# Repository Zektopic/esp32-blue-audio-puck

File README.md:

# BlueAudio Puck

**Turn wired headphones wireless.** A pocket-sized Bluetooth audio receiver: it
pairs with a phone or computer as an A2DP sink, decodes the stream on an ESP32,
runs it through a parametric equaliser, and pushes PCM out over I²S to an
external DAC and headphone amplifier feeding a 3.5 mm jack.

-informational)

> [!IMPORTANT]
> **Original ESP32 only.** A2DP rides on Bluetooth Classic (BR/EDR), which
> Espressif removed from the ESP32-S3 and ESP32-C3. Those parts are BLE-only and
> cannot run this firmware — and they cannot fall back to LE Audio either, since
> that needs BLE 5.2 isochronous channels and they are 5.0.

---

## What it does

| | |
| --- | --- |
| **A2DP sink** | Pairs as a headphone. SBC decode, 16/32/44.1/48 kHz, mono or stereo. |
| **I²S output** | 16-bit PCM to an external DAC. APLL-clocked for accurate 44.1 kHz. |
| **AVRCP, both roles** | Phone's volume slider works; track metadata comes back; buttons drive transport. |
| **Parametric EQ** | Five biquad bands per channel, sample-rate aware, ~16% of one core when fully active. |
| **OLED status screen** | 128x64 SSD1306 over I2C: signal, track, artist, transport, volume, battery. |
| **Battery gauge** | ADC on a divider, Li-po curve, low and critical warnings. |
| **Physical UI** | One multi-function button, optional volume keys, optional PWM status LED. |
| **Power policy** | Capped TX power, 80–160 MHz frequency scaling, deep sleep on idle. |
| **Bounded pairing** | Discoverable only when you ask for it, not permanently. |

## Signal chain

```mermaid
flowchart LR
    SRC["Phone / PC<br/><i>A2DP source</i>"]
    subgraph PUCK["BlueAudio Puck"]
        direction LR
        BT["ESP32<br/>Bluedroid A2DP sink<br/>SBC decode"]
        DSP["Ring buffer<br/>+ EQ + volume"]
        DAC["PCM5102A<br/>I²S DAC"]
        AMP["Headphone amp"]
        OLED["SSD1306 OLED<br/><i>I²C</i>"]
        BATT["Li-po + divider<br/><i>ADC</i>"]
    end
    JACK["3.5 mm<br/>headphones"]

    SRC -- "Bluetooth Classic" --> BT
    BT -- "PCM frames" --> DSP
    DSP -- "I²S" --> DAC
    DAC -- "line level" --> AMP
    AMP --> JACK
    BT -. "track, volume" .-> OLED
    BATT -. "percent" .-> OLED
```

## Firmware architecture

The single rule everything else follows: **Bluedroid callbacks only enqueue.**
Anything slow in stack context stalls the radio and comes out as dropouts.

```mermaid
flowchart TD
    subgraph BTCTX["Bluetooth stack context — never blocks"]
        A2DP["A2DP data callback"]
        EVT["GAP / A2DP / AVRCP<br/>event callbacks"]
    end
    subgraph APPCTX["Application task — core 0"]
        WORK["work dispatcher<br/><i>bt_core</i>"]
    end
    subgraph AUDCTX["Audio writer task — core 1"]
        RB[("ring buffer<br/>32 kB")]
        EQ["biquad cascade<br/><i>audio_dsp</i>"]
        VOL["volume gain"]
        I2S["i2s_channel_write"]
    end

    A2DP -- "non-blocking send" --> RB
    EVT -- "dispatch" --> WORK
    WORK -- "start / stop / format" --> RB
    RB --> EQ --> VOL --> I2S

    classDef ctx fill:none,stroke-dasharray:4 3
    class BTCTX,APPCTX,AUDCTX ctx
```

Every cost — the blocking I²S write, the EQ, the gain — lives on the writer
task, pinned to the core the radio is not using.

### Components

| Component | Responsibility |
| --- | --- |
| [`bt_core`](components/bt_core/) | Stack bring-up, work queue between Bluedroid and the app task, bond management |
| [`audio_sink`](components/audio_sink/) | I²S channel, ring buffer, writer task, volume gain |
| [`audio_dsp`](components/audio_dsp/) | Parametric biquad equaliser and its benchmark |
| [`puck_avrcp`](components/puck_avrcp/) | AVRCP controller and target: volume, metadata, transport keys |
| [`puck_ui`](components/puck_ui/) | Button gestures and PWM status LED |
| [`puck_display`](components/puck_display/) | SSD1306 panel driver, framebuffer, screens |
| [`puck_battery`](components/puck_battery/) | ADC sensing and the Li-po discharge curve |
| [`puck_power`](components/puck_power/) | TX power, frequency scaling, idle deep sleep |

These are written from scratch against the IDF v5.5 API rather than reusing the
ESP-IDF example's shared components, which are pulled in by `${IDF_PATH}` path
and would make the repository unbuildable anywhere else. See
[docs/design-notes.md](docs/design-notes.md) for what that surfaced.

## Hardware

The pin map follows the layout that lets a PCM5102A board sit **directly under**
an ESP32 devkit on short solder bridges, rather than the pins that happen to be
convenient on a breadboard.

| ESP32 | Signal | Goes to |
| --- | --- | --- |
| GPIO 4 | I²S BCK | PCM5102A `BCK` |
| GPIO 15 | I²S LRCK | PCM5102A `LRCK` |
| GPIO 2 | I²S DATA | PCM5102A `DIN` |
| GPIO 21 | I²C SDA | SSD1306 `SDA` |
| GPIO 22 | I²C SCL | SSD1306 `SCL` |
| GPIO 32 | BT1 | to GND — next track / volume up |
| GPIO 33 | BT2 | to GND — play/pause / pairing (RTC pin, wakes from deep sleep) |
| GPIO 27 | BT3 | to GND — previous track / volume down |
| GPIO 35 | Battery sense | divider midpoint (optional, unfitted by default) |
| 3V3, GND | Power | both boards |

> [!NOTE]
> **No MCLK/SCK wire to the DAC.** Solder the `SCK` bridge on the front of the
> PCM5102A instead and it derives its own clock from BCK. Leave the ESP32 pin
> beneath it unconnected — a strip of tape stops it shorting to anything.

> [!IMPORTANT]
> **GPIO 2 is the devkit's on-board LED pin and a strapping pin.** It now
> carries I²S data, so the on-board LED flickers with audio — harmless, and the
> reason `PUCK_LED_GPIO` defaults to *not fitted*. It also means the board may
> refuse to enter download mode if the DAC holds that line high during reset;
> holding **BOOT** while flashing works around it.

PCM5102A jumpers — these cause most "no sound" reports:

| Pin | Set to | Why |
| --- | --- | --- |
| SCK bridge | **soldered** | Runs the internal PLL, so no MCLK wire is needed |
| XSMT | 3V3 | Release soft-mute. Low means muted. |
| FMT | GND | I²S (Philips) frame format, which is the firmware default |
| FLT | GND | Normal latency filter |
| DEMP | GND | De-emphasis off |

**Battery sensing** is optional and off by default. To fit it, run a divider
from the cell to GPIO 35 — two 100 kΩ resistors give 2:1, fits the ADC range
with a full 4.2 V cell, and draws about 21 µA — then set
`PUCK_BATTERY_ADC_GPIO=35` and the ratio to match your resistors.

Full parts discussion, power budget and the roadmap to a custom board:
[docs/hardware.md](docs/hardware.md).

## Building

Requires **ESP-IDF v5.5.4**.

```powershell
& 'C:\Espressif\tools\Microsoft.v5.5.4.PowerShell_profile.ps1'
idf.py set-target esp32
idf.py build
idf.py -p COM10 flash monitor
```

`sdkconfig` is generated and gitignored; `sdkconfig.defaults` is the source of
truth. Project settings live under **BlueAudio Puck** in `idf.py menuconfig`.

Expected first output:

```
I (593) puck: BlueAudio Puck booting (IDF v5.5.4)
I (603) audio_sink: ready: bck=4 ws=15 dout=2, 32 kB buffer, prefetch 25%
I (603) audio_dsp: 5-band equaliser ready at 44100 Hz (off, 0 active)
I (613) ssd1306: 128x64 panel at 0x3c on SDA=21 SCL=22
I (1313) bt_core: controller up, address ...
I (1373) puck: no bonded sources; discoverable as "BlueAudio Puck"
```

> [!TIP]
> If flashing fails with `Wrong boot mode detected (0x13)`, hold the **BOOT**
> button as the flash starts. Some devkits — and any board where GPIO 2 is
> loaded by the DAC — will not auto-reset into download mode.

## Using it

| Button | Tap | Hold |
| --- | --- | --- |
| **BT1** | Next track | Volume up — repeats while held |
| **BT2** | Play / pause | Pairing window (1.5 s) · forget all bonds (5 s) |
| **BT3** | Previous track | Volume down — repeats while held |

One action per press, no multi-tap timing to get right. Holding a volume button
sweeps rather than nudging once, at roughly four seconds end to end.

### The screen

| Screen | When |
| --- | --- |
| Splash | While the stack comes up |
| `PAIRING` | Discoverable, waiting for a source |
| `IDLE` | Connectable, nothing connected |
| Now playing | Signal, track and artist, transport state, volume bar, battery |

The top-left **signal meter** shows link quality while a source is connected.
It is hidden when nothing is connected, because bars against no link would be
meaningless. Note what Bluetooth Classic actually reports — see below.

The track title scrolls when it is too long, pausing at each end — continuous
sliding is much harder to read. Volume changes raise a brief toast over the
bottom of the screen. Battery shows as a percentage and an icon, or `USB` when
no sense divider is fitted.

> [!NOTE]
> **The signal meter will usually read full, and that is correct.** Bluetooth
> Classic does not report absolute signal strength. It reports a delta from the
> *Golden Receive Power Range* — the window the controller works to keep the
> link inside — so **zero means healthy**, not "no signal". The value only goes
> negative once the link is genuinely struggling. Read the bars as *fine /
> getting worse / about to drop out*, not as dBm.

At start-up the panel runs a **self test** — solid fill, checkerboard, then a
border — before any text is drawn. None of it uses the font, which is the
point: it separates a bus or panel fault from a text-rendering fault.

### The optional LED

| LED | Meaning |
| --- | --- |
| Fast blink | Discoverable, waiting for a source |
| Slow breathe | Connected, not streaming |
| Steady dim | Audio playing |
| Triple flash | Something failed to start |

Unfitted by default, because GPIO 2 now carries I²S data and the screen shows
the same states in words.

Volume normally comes from the phone over AVRCP absolute volume. Dedicated
volume buttons are optional and unfitted by default.

## Configuration

All under `idf.py menuconfig` → **BlueAudio Puck**. Every GPIO accepts `-1` for
"not fitted".

| Option | Default | Notes |
| --- | --- | --- |
| `PUCK_BT_DEVICE_NAME` | `BlueAudio Puck` | Shown in the pairing list |
| `PUCK_I2S_BCK/LRCK/DOUT_GPIO` | 4 / 15 / 2 | Direct-solder layout |
| `PUCK_I2C_SDA/SCL_GPIO` | 21 / 22 | `-1` disables the display |
| `PUCK_DISPLAY_I2C_ADDRESS` | 0x3C | Some modules strap to 0x3D |
| `PUCK_DISPLAY_CONTRAST` | 127 | |
| `PUCK_DISPLAY_SELF_TEST` | on | ~1.4 s of boot time |
| `PUCK_RSSI_POLL_SECONDS` | 3 | How often the signal meter updates |
| `PUCK_BATTERY_ADC_GPIO` | 35 | ADC1 pins only (32–39); `-1` if no divider |
| `PUCK_BATTERY_DIVIDER_RATIO_X100` | 200 | 2:1; must match your resistors |
| `PUCK_BT1/BT2/BT3_GPIO` | 32 / 33 / 27 | Active low, internal pull-up |
| `PUCK_VOLUME_STEP` | 6 | Per repeat, of 127 |
| `PUCK_LED_GPIO` | -1 | GPIO 2 is now I²S data |
| `PUCK_I2S_SLOT_FORMAT` | Philips | Must match the DAC's `FMT` pin |
| `PUCK_I2S_USE_APLL` | on | Accurate 44.1 kHz, slightly more current |
| `PUCK_AUDIO_RINGBUF_KB` | 32 | Larger rides out radio retries, costs RAM and latency |
| `PUCK_AUDIO_PREFETCH_PERCENT` | 25 | ≈46 ms cushion; also what an underrun costs to rebuild |
| `PUCK_AUDIO_WRITER_CORE` | 1 | Keep off core 0, which runs the radio |
| `PUCK_EQ_BANDS` | 5 | A ceiling, not a fixed price — flat bands cost nothing |
| `PUCK_EQ_ENABLED_AT_BOOT` | off | Starts transparent |
| `PUCK_EQ_BENCHMARK_AT_BOOT` | off | Times the cascade; see below |
| `PUCK_PAIRING_WINDOW_SECONDS` | 120 | How long a long press stays discoverable |
| `PUCK_BT_TX_POWER_LEVEL` | 7 (+9 dBm) | Ceiling; lower it for runtime |
| `PUCK_BT_TX_POWER_MIN_LEVEL` | 4 (0 dBm) | Floor power control may drop to |
| `PUCK_CPU_MAX/MIN_FREQ_MHZ` | 160 / 80 | Dynamic frequency scaling |
| `PUCK_IDLE_SLEEP_MINUTES` | 15 | Counts only while disconnected; 0 disables |

## Measured

| What | Result |
| --- | --- |
| EQ cost, 5 stereo biquad sections | 1337 µs per 360-frame block = **16% of one core** at 160 MHz |
| EQ cost per band | ~3.2% of a core, so roughly 30 sections before saturating one |
| OLED bus scan | One device ACKs at **0x3C** on SDA 21 / SCL 22 |
| Full-frame OLED refresh | 1025 bytes at 400 kHz ≈ 21 ms, hence a few Hz refresh |
| Firmware image | ~1.04 MB (needs the large single-app partition; the 1 MB default does not fit) |
| Free heap after boot | ~210 kB |
| Pairing window | Closes at 120.0 s, verified on hardware |

Power draw has **not** been measured. The estimates in
[docs/hardware.md](docs/hardware.md) are datasheet-derived, and devkit
measurements would be meaningless anyway — the USB-UART bridge and the AMS1117
regulator dominate a devkit's draw whatever the firmware does.

## Documentation

- [hardware/](hardware/) — KiCad schematic and PCB for a single-board version (unrouted, unfabricated)
- [docs/hardware.md](docs/hardware.md) — parts, wiring, power budget, board roadmap
- [docs/design-notes.md](docs/design-notes.md) — why the firmware is shaped this way, and the IDF bugs it avoids
- [docs/troubleshooting.md](docs/troubleshooting.md) — no sound, no pairing, dropouts, build failures
- [SECURITY.md](SECURITY.md) — threat model, pairing decisions, accepted risks

## Status

Working: builds, boots, pairs, advertises correctly, AVRCP negotiates, power and
UI subsystems initialise. Verified on an ESP32-WROOM devkit.

**Not yet verified:** audio actually coming out, and what the OLED renders. The
I²C bus and the panel address are confirmed by a scan on real hardware, but the
glyphs and layout have not been seen. The I²S configuration, the EQ response and
the end-to-end audio path are reasoned against the ESP-IDF v5.5.4 driver
sources, not heard. Battery sensing has no cell fitted, so only its
"not fitted" path runs.

## Prior art

Written from scratch, but these informed the design and are worth reading:

- [WillyBilly06/ESP32-A2DP-SINK-WITH-CODECS-UPDATED](https://github.com/WillyBilly06/ESP32-A2DP-SINK-WITH-CODECS-UPDATED) — LDAC/aptX/AAC patched into the IDF stack, which proves the SBC ceiling is firmware and not silicon
- [YetAnotherElectronicsChannel/ESP32_4CH_DSP_BT_AMPLIFIER](https://github.com/YetAnotherElectronicsChannel/ESP32_4CH_DSP_BT_AMPLIFIER) — parametric EQ with a Wi-Fi config UI, full schematics and gerbers
- [ESP32 as BT receiver with DSP capabilities](https://hackaday.io/project/166122-esp32-as-bt-receiver-with-dsp-capabilities) — biquads in the a2dp_sink render path; left the biquad budget as an open question, which [docs/design-notes.md](docs/design-notes.md) answers
- [gangg111/ESP32-Bluetooth-Audio-Receiver](https://github.com/gangg111/ESP32-Bluetooth-Audio-Receiver) — PCM5102A plus an OLED showing track metadata
- [pschatzmann/ESP32-A2DP](https://github.com/pschatzmann/ESP32-A2DP) — the reference Arduino-side A2DP library

## Licence

MIT — see [LICENSE](LICENSE).

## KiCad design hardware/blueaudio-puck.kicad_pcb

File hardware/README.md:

# BlueAudio Puck carrier board, rev A

KiCad 10 schematic and PCB for a single-board version of the puck: ESP32-WROOM-32U,
PCM5102A DAC, Li-po charging, two separate 3V3 rails, OLED header, three user
buttons and a 3.5 mm output — 60 × 64 mm, drawn to JLCPCB's two-layer rules.

| File | What it is |
| --- | --- |
| [`blueaudio-puck.kicad_pro`](blueaudio-puck.kicad_pro) | Project — open this |
| [`blueaudio-puck.kicad_sch`](blueaudio-puck.kicad_sch) | Schematic |
| [`blueaudio-puck.kicad_pcb`](blueaudio-puck.kicad_pcb) | Board |
| [`bom.csv`](bom.csv) | Bill of materials |
| [`preview/`](preview/) | SVG renders of both |
| [`scripts/`](scripts/) | The generator — see below |

## Read this before you order anything

> [!CAUTION]
> **Not finished: eight nets still need routing by hand.**
>
> Everything the generator lays is DRC-clean — **zero clearance violations,
> zero shorts, zero hole-clearance errors** under JLCPCB's rules. But 25 of 33
> nets are routed, not 33, and the remaining eight are unconnected copper:
>
> `+3V3A` · `AUDIO_L` · `CC1` · `CC2` · `DAC_LDOO` · `DAC_VNEG` · `I2S_BCK` · `I2S_LRCK`
>
> All eight are around the two fine-pitch parts — the TSSOP-20 DAC and the
> USB-C receptacle. Open the board in Pcbnew and its interactive router will
> finish them far faster and better than the one in `scripts/`. Do not order
> anything until DRC reports zero unconnected items.

> [!WARNING]
> **Nothing here has been fabricated or tested.** It passes ERC and the DRC
> checks that apply to an unrouted board. It has never been a physical object.
> Review the schematic against the datasheets before you spend money.

## Verification

Actually run, with the output quoted rather than summarised:

```
$ kicad-cli sch erc --severity-error --severity-warning
Found 4 violations                    # all lib_symbol_mismatch, see below

$ kicad-cli pcb drc --severity-error --severity-warning
Found 25 violations
Found 22 unconnected items
```

The schematic is clean: **zero electrical errors**, no unconnected pins, no
dangling labels, no malformed outline. All four ERC warnings are
`lib_symbol_mismatch` on KiCad's *derived* symbols — the two regulators and the
two transistors. Cosmetic; see below.

The board has **no electrical errors either**. Breaking the 25 down:

| Count | Kind | Status |
| --- | --- | --- |
| 22 | `unconnected_items` | **Must fix** — the eight unrouted nets |
| 15 | `silk_over_copper` | Cosmetic; every fab ignores it |
| 10 | `silk_overlap` | Cosmetic |

No `clearance`, no `shorting_items`, no `hole_clearance`. That took three fixes
to the router's geometry, each of which had produced copper that looked right
and was not — they are written up in the file that makes them:

- **A track is not a point.** A 0.4 mm power track centred on a 0.25 mm grid
  cell spills into its neighbours; checking only the cell it steps through let
  it sit 0.15 mm from a pad. Same for vias, which are 0.6 mm across — one
  landed on top of another net's track.
- **Clearance belongs in the check, not the map.** Growing a clearance halo
  around every pad *and* checking a track's own clearance against it demanded
  the gap twice, which makes escaping a 0.65 mm pitch TSSOP impossible.
- **Holes are stricter than copper.** Copper-to-hole is 0.25 mm where
  copper-to-copper is 0.15 mm, so drilled pads are claimed slightly larger than
  their copper.

The router still gets 25 of 33 nets rather than all of them. It routes in order
and never rips up an earlier net to make room, which is the difference between
it and a real autorouter.

The two ERC warnings are `lib_symbol_mismatch` on `AP2112K-3.3` and
`LP2985-3.3`. Both are KiCad *derived* symbols (`extends`), and the generator
flattens them to embed them; the flattened copy differs cosmetically from the
library's. Connectivity and pin numbering are unaffected. Eeschema's
*Update Symbols from Library* clears it.

The silkscreen warnings are reference designators sitting over pads. Normal for
auto-placed boards, ignored by every fab, and worth tidying only once placement
is final.

## How it is generated

Both files come from **one** netlist, in [`scripts/design.py`](scripts/design.py).

That matters more than it sounds. A schematic and a PCB authored separately
disagree about connectivity, and KiCad does not tell you until someone runs ERC
and gets a wall of errors. One source, two emitters, no drift.

```
scripts/design.py         parts, nets, no-connects, board size  <- edit this
scripts/kisym.py          pulls symbols out of the KiCad libraries
scripts/check_sheet.py    catches stubs from different nets touching
scripts/gen_schematic.py  emits the .kicad_sch
scripts/gen_pcb.py        emits the .kicad_pcb (needs KiCad's python)
```

To regenerate:

```bash
cd hardware/scripts
python design.py          # netlist self-check
python check_sheet.py     # no two nets touching
python gen_schematic.py
"C:/Users/manup/AppData/Local/Programs/KiCad/10.0/bin/python.exe" gen_pcb.py
```

`gen_pcb.py` needs KiCad's bundled interpreter — `pcbnew` lives only there.

Symbols and footprints are copied from the installed libraries rather than
transcribed, so the output files are self-contained and open on a machine with
no libraries configured. A hand-typed pin table is exactly the kind of error
nothing but a human eye can catch.

### Once you edit it by hand

The generators overwrite their outputs. Move the files out of `hardware/`, or
stop regenerating, once you start editing in KiCad — which you will, because
routing is the next step.

## The design

```
USB-C ──> MCP73831 ──> Li-po ──┬──> AP2112K ──> +3V3  ──> ESP32, OLED, DAC digital
                               └──> LP2985  ──> +3V3A ──> DAC analogue
```

**Two regulators from the cell, not one.** The DAC's analogue rail gets its own
low-noise LP2985 with a bypass capacitor. Sharing a rail with a Bluetooth radio
is what makes a DAC hiss, and `docs/hardware.md` said so before this board
existed.

**No MCLK.** The PCM5102A has `SCK` grounded and runs from its internal PLL,
matching the hand-built prototype and what the firmware expects.

**JP1 sits in series with I²S data on GPIO 2.** That pin is a boot strapping
pin, and a DAC loading it is why the prototype needs BOOT held to flash. Lift
the jumper and the board flashes normally.

**Battery sense** is R7/R8, a 2:1 divider into GPIO 35, matching
`PUCK_BATTERY_DIVIDER_RATIO_X100=200`.

**Three user buttons** on GPIO 32/33/27, matching the firmware — SW1 is BT1
(next / volume up), SW2 is BT2 (play-pause / pairing), SW3 is BT3 (previous /
volume down). All active low straight to ground; the ESP32's internal pull-ups
mean no external resistors. SW4 and SW5 are RESET and BOOT.

Note there is **no LED on GPIO 27** on this board. The Kconfig help for
`PUCK_LED_GPIO` suggests 27 for an external status LED, which would collide
with BT3 on a breadboard. Here the only LED is D1, the charge indicator on
`CHG_STAT`, so GPIO 27 is unambiguously BT3.

### Where it departs from `docs/hardware.md`

Both departures are deliberate and both are rev B work:

**No buck-boost.** `docs/hardware.md` specifies a TPS63020 for efficiency —
roughly 20–25% more runtime than an LDO. KiCad's standard library has no symbol
for it, and inventing one is precisely the silent error this generator exists to
avoid. Rev A uses LDOs and pays the efficiency.

**No headphone amplifier.** The PCM5102A is line level: audible on 32 Ω
headphones but quiet, exactly as the docs warn. A TPA6132A2 is the rev B
addition, and it is QFN-16 — it would make this board far harder to hand-build.

## Manufacturing rules

Written into the project file, so DRC enforces them rather than leaving them as
folklore. JLCPCB's standard two-layer process, with margin:

| | JLC minimum | Used here |
| --- | --- | --- |
| Track width | 0.127 mm | 0.20 mm |
| Clearance | 0.127 mm | 0.15 mm |
| Via drill | 0.20 mm | 0.30 mm |
| Via diameter | drill + 0.26 | 0.60 mm |
| Annular ring | 0.13 mm | 0.15 mm |
| Hole to hole | 0.50 mm | 0.50 mm |
| Track to outline | 0.20 mm | 0.50 mm |

Only clearance sits near a limit, and it is still 18% above JLC's floor. The
0.05 mm it frees up per side compared with KiCad's 0.2 mm default is most of
what lets the congested area route at all.

**Teardrops are configured but not generated.** The parameters are in the
project file; KiCad adds the actual teardrops on demand. Run *Edit → Teardrops
→ Add Teardrops* in Pcbnew once routing is finished — doing it before then
would only have to be redone.

## What is left to do

1. **Route the last eight nets** in Pcbnew: `+3V3A`, `AUDIO_L`, `CC1`, `CC2`,
   `DAC_LDOO`, `DAC_VNEG`, `I2S_BCK`, `I2S_LRCK`. All are around the TSSOP-20
   DAC and the USB-C part. The interactive router will do this in minutes.
2. **Add teardrops** once routing is done.
3. **Check the antenna keep-out.** The WROOM-32U has an external connector so
   there is no PCB antenna to clear, but leave the module's edge unpoured.
4. **Re-run DRC** and get it to zero before ordering anything.
5. **Review against datasheets.** Especially the MCP73831 programming resistor
   (R5 = 2 kΩ, about 500 mA) against your cell's charge rate.
6. **Rounded corners** were dropped — arcs whose endpoints did not meet left the
   outline open, and KiCad will not guess. Add them in Pcbnew, where the editor
   keeps the ends joined.

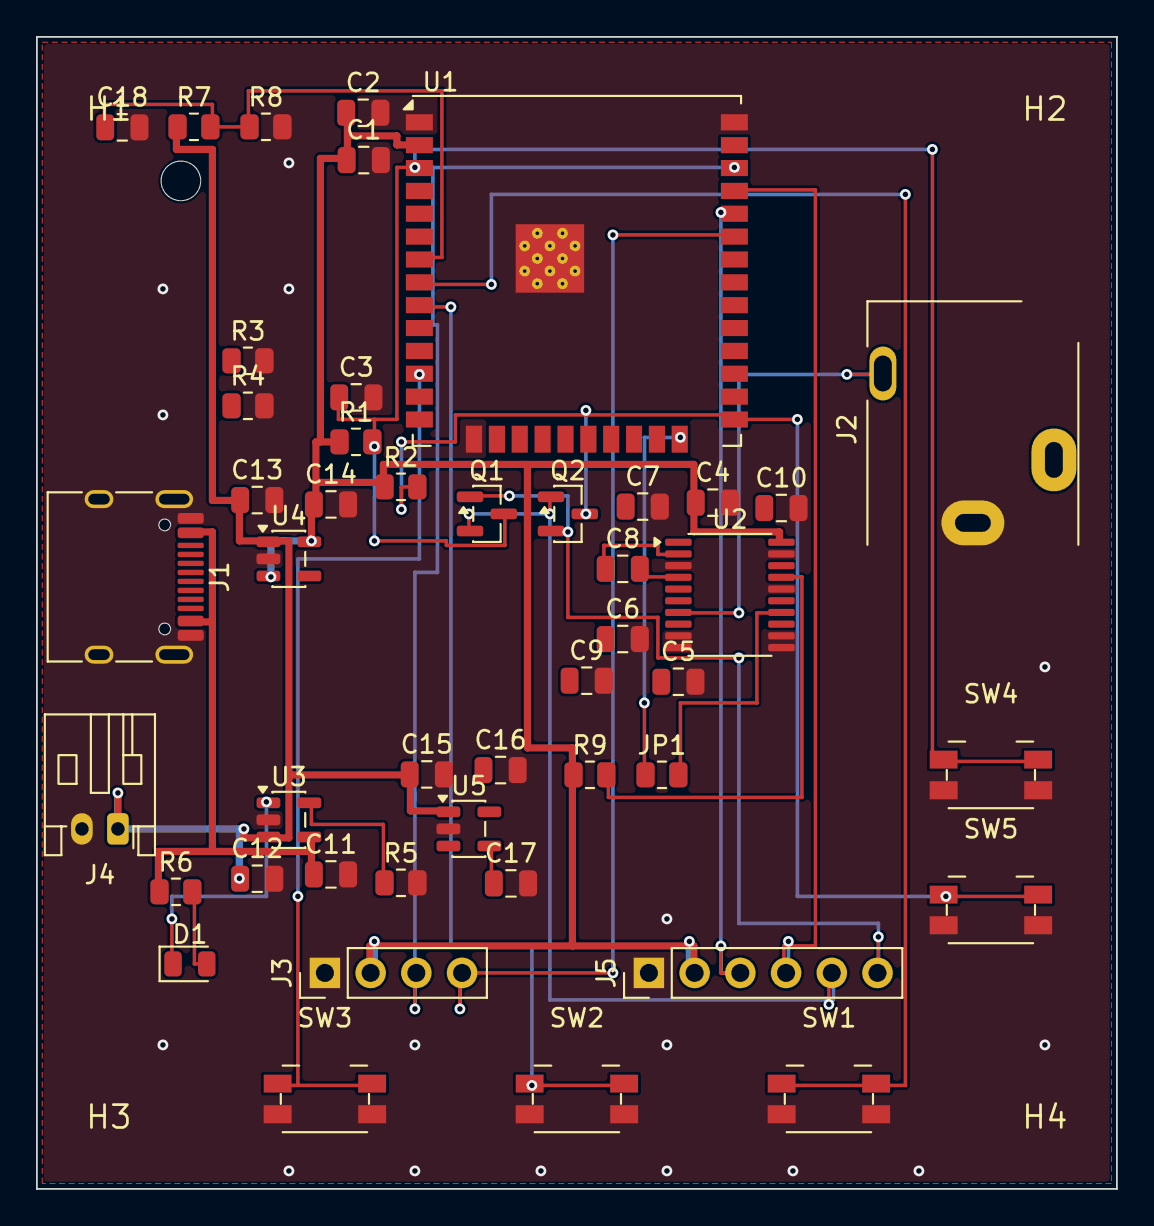
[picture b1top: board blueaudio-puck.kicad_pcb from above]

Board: 2 copper layers, 60.0 x 64.0 mm, 50 parts (0 on the bottom side), 34 nets.

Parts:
C1, C4, C5, C7, C10, C18: 100n; C_0805_2012Metric
C2, C6, C14, C16: 10u; C_0805_2012Metric
C3, C8, C9, C11, C13, C15: 1u; C_0805_2012Metric
C12: 4u7; C_0805_2012Metric
C17: 10n; C_0805_2012Metric
D1: CHG; LED_0805_2012Metric
H1, H2, H3, H4: (no value)
J1: USB-C; USB_C_Receptacle_HRO_TYPE-C-31-M-12
J2: 3.5mm; Jack_3.5mm_CUI_SJ1-3513N_Horizontal
J3: OLED; PinHeader_1x04_P2.54mm_Vertical
J4: BATT; JST_PH_S2B-PH-K_1x02_P2.00mm_Horizontal
J5: PROG; PinHeader_1x06_P2.54mm_Vertical
JP1: 0R; R_0805_2012Metric
Q1, Q2: MMBT3904; SOT-23
R1, R2, R9: 10k; R_0805_2012Metric
R3, R4: 5k1; R_0805_2012Metric
R5: 2k; R_0805_2012Metric
R6: 1k; R_0805_2012Metric
R7, R8: 100k; R_0805_2012Metric
SW1: BT1; Panasonic_EVQPUJ_EVQPUA
SW2: BT2; Panasonic_EVQPUJ_EVQPUA
SW3: BT3; Panasonic_EVQPUJ_EVQPUA
SW4: RESET; Panasonic_EVQPUJ_EVQPUA
SW5: BOOT; Panasonic_EVQPUJ_EVQPUA
U1: ESP32-WROOM-32U
U2: PCM5102A; TSSOP-20_4.4x6.5mm_P0.65mm
U3: MCP73831-2-OT; SOT-23-5
U4: AP2112K-3.3; SOT-23-5
U5: LP2985-3.3; SOT-23-5

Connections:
+3V3: C1.1, C2.1, C4.1, C14.1, J3.2, J5.2, R1.1, R2.1, R9.1, U1.2, U2.20, U4.3, U4.5
+3V3A: C5.1, C6.1, C7.1, C16.1, U2.1, U2.8, U5.3, U5.5
AUDIO_L: J2.T, U2.6
AUDIO_R: J2.R, U2.7
BTN_1: SW1.1, U1.8
BTN_2: SW2.1, U1.9
BTN_3: SW3.1, U1.12
CC1: J1.A5, R3.1
CC2: J1.B5, R4.1
CHG_LED_A: D1.2, R6.2
CHG_PROG: R5.1, U3.5
CHG_STAT: D1.1, U3.1
DAC_CAPM: C8.2, U2.4
DAC_CAPP: C8.1, U2.2
DAC_LDOO: C10.1, U2.18
DAC_VNEG: C9.1, U2.5
DAC_XSMT: R9.2, U2.17
DTR: J5.5, Q1.2, Q2.1
EN: C3.1, Q1.3, R1.2, SW4.1, U1.3
GND: C1.2, C2.2, C3.2, C4.2, C5.2, C6.2, C7.2, C9.2, C10.2, C11.2, C12.2, C13.2, C14.2, C15.2, C16.2, C17.2, C18.2, J1.A1, J1.A12, J1.B1, J1.B12, J1.SH, J2.S, J3.1, J4.2, J5.1, R3.2, R4.2, R5.2, R8.2, SW1.2, SW2.2, SW3.2, SW4.2, SW5.2, U1.1, U1.15, U1.38, U1.39, U2.3, U2.9, U2.10, U2.11, U2.12, U2.16, U2.19, U3.2, U4.2, U5.2
I2C_SCL: J3.3, U1.36
I2C_SDA: J3.4, U1.33
I2S_BCK: U1.26, U2.13
I2S_DATA: JP1.2, U2.14
I2S_DATA_MCU: JP1.1, U1.24
I2S_LRCK: U1.23, U2.15
IO0: Q2.3, R2.2, SW5.1, U1.25
RTS: J5.6, Q1.1, Q2.2
RXD0: J5.3, U1.34
TXD0: J5.4, U1.35
U5_BYPASS: C17.1, U5.4
VBAT: C12.1, C13.1, C15.1, J4.1, R7.1, U3.3, U4.1, U5.1
VBAT_SENSE: C18.1, R7.2, R8.1, U1.7
VBUS: C11.1, J1.A4, J1.A9, J1.B4, J1.B9, R6.1, U3.4

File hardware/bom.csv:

"Reference","Value","Footprint","QUANTITY"
"C1,C4,C5,C7,C10,C18","100n","Capacitor_SMD:C_0805_2012Metric","6"
"C2,C6,C14,C16","10u","Capacitor_SMD:C_0805_2012Metric","4"
"C3,C8,C9,C11,C13,C15","1u","Capacitor_SMD:C_0805_2012Metric","6"
"C12","4u7","Capacitor_SMD:C_0805_2012Metric","1"
"C17","10n","Capacitor_SMD:C_0805_2012Metric","1"
"D1","CHG","LED_SMD:LED_0805_2012Metric","1"
"J1","USB-C","Connector_USB:USB_C_Receptacle_HRO_TYPE-C-31-M-12","1"
"J2","3.5mm","Connector_Audio:Jack_3.5mm_CUI_SJ1-3513N_Horizontal","1"
"J3","OLED","Connector_PinHeader_2.54mm:PinHeader_1x04_P2.54mm_Vertical","1"
"J4","BATT","Connector_JST:JST_PH_S2B-PH-K_1x02_P2.00mm_Horizontal","1"
"J5","PROG","Connector_PinHeader_2.54mm:PinHeader_1x06_P2.54mm_Vertical","1"
"JP1","0R","Resistor_SMD:R_0805_2012Metric","1"
"Q1,Q2","MMBT3904","Package_TO_SOT_SMD:SOT-23","2"
"R1,R2,R9","10k","Resistor_SMD:R_0805_2012Metric","3"
"R3,R4","5k1","Resistor_SMD:R_0805_2012Metric","2"
"R5","2k","Resistor_SMD:R_0805_2012Metric","1"
"R6","1k","Resistor_SMD:R_0805_2012Metric","1"
"R7,R8","100k","Resistor_SMD:R_0805_2012Metric","2"
"SW1","BT1","Button_Switch_SMD:Panasonic_EVQPUJ_EVQPUA","1"
"SW2","BT2","Button_Switch_SMD:Panasonic_EVQPUJ_EVQPUA","1"
"SW3","BT3","Button_Switch_SMD:Panasonic_EVQPUJ_EVQPUA","1"
"SW4","RESET","Button_Switch_SMD:Panasonic_EVQPUJ_EVQPUA","1"
"SW5","BOOT","Button_Switch_SMD:Panasonic_EVQPUJ_EVQPUA","1"
"U1","ESP32-WROOM-32U","RF_Module:ESP32-WROOM-32U","1"
"U2","PCM5102A","Package_SO:TSSOP-20_4.4x6.5mm_P0.65mm","1"
"U3","MCP73831-2-OT","Package_TO_SOT_SMD:SOT-23-5","1"
"U4","AP2112K-3.3","Package_TO_SOT_SMD:SOT-23-5","1"
"U5","LP2985-3.3","Package_TO_SOT_SMD:SOT-23-5","1"

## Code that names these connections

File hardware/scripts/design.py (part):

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    Note there is no LED on GPIO 27 here. The Kconfig help for PUCK_LED_GPIO
    suggests 27 for an external status LED, which would collide with BT3 on a
    breadboard -- on this board the only LED is D1, the charge indicator on
    CHG_STAT, so the pin is unambiguously BT3.
  * JP1 sits in series with I2S data on GPIO 2. That pin is a boot strapping
    pin, and a DAC loading it is why the prototype needs BOOT held to flash.
    Lift the jumper and the board flashes normally.
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    Reasoning about a cross-coupled pair from memory is how people ship boards
    that reset every time a terminal opens. This reads the actual connectivity
    -- which net is on each transistor's base, emitter and collector -- and
    works out what happens for all four DTR/RTS combinations. MMBT3904 pins are
    1=B, 2=E, 3=C.
    """
    mapping = pin_to_net()
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

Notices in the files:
README.md:
License: MIT
